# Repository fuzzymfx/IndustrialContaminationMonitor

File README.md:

Industrial pollutants are mainly discharged from various origins such as pulp and paper mills, chemical fertilizers, oil refineries, sugar factories, tanneries, textiles, steel, distilleries, fertilizers, pesticides, coal and mineral mining industries, drugs, glass, cement, petroleum, and engineering industries etc. 

Most of the industries dump via transporter to dumping places and thus there is no necessity for a check in the industry itself. The people staying nearby often utilize the same land and water for agricultural and daily purposes.  We believe that the industries should not take things lightly and especially for people staying nearby and the workers of the place a check should be there which when is necessary, warns the area of the contamination in soil and water. Industries have always had an intelligent solution about this. Dumping pipes always had a solvent which would dissolve the contamination if the level increases. This process is called neutralization But, this never gave the locals and the workers about information or statistical data about the amount of contamination currently present in the surroundings, instead all they get to know that the solvent is doing its job. We aim to target this problem by cost effective solutions.

We are trying to design a device which will measure the soil, water and air contamination in the area and warn the industries and local people when contamination limit exceeds. We are trying to make cost efficient product using IOT.
Budget:

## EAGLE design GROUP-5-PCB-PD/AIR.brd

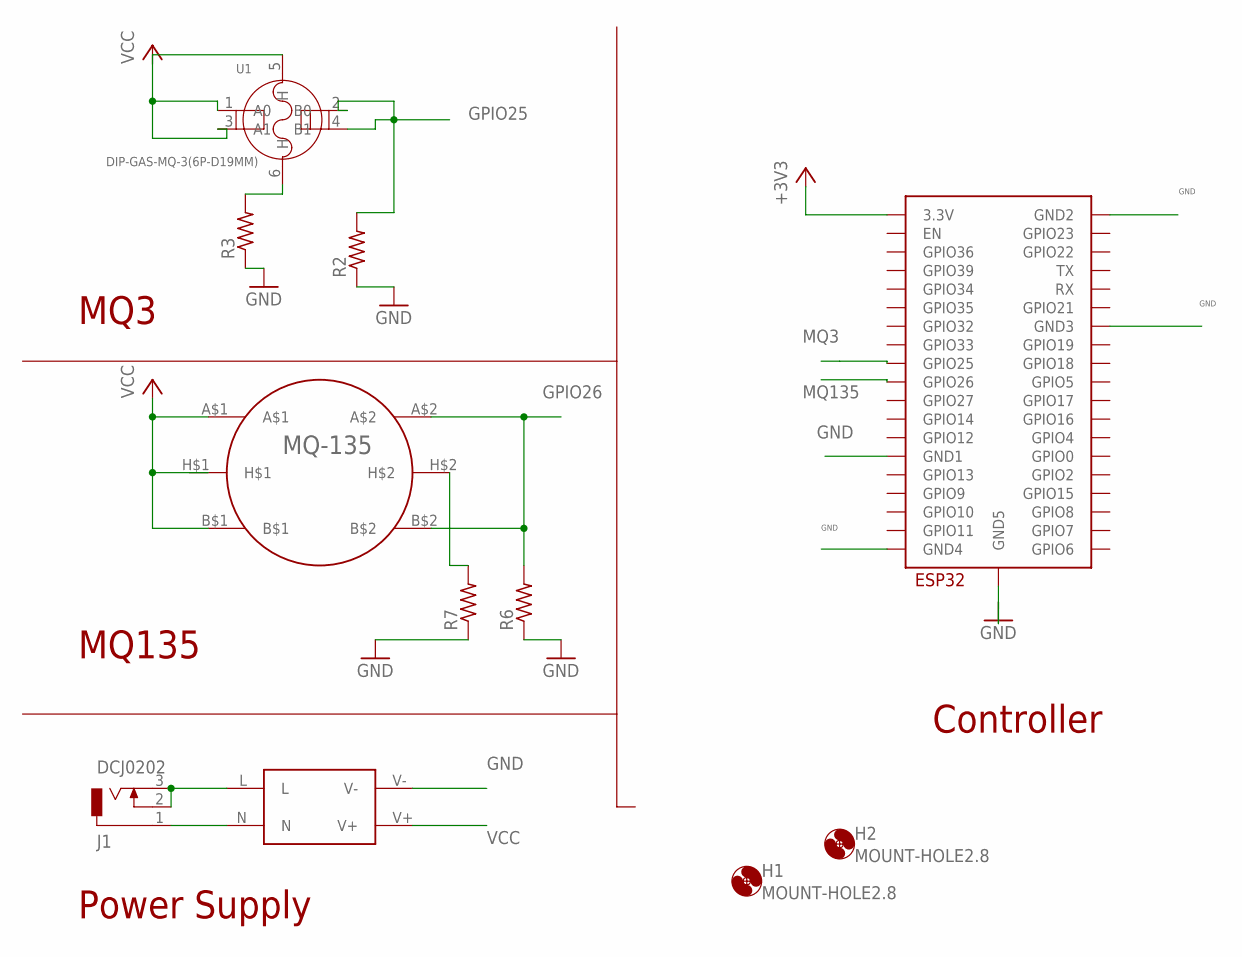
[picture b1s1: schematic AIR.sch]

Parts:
H1, H2: MOUNT-HOLE2.8; 2,8
J1: DCJ0202
R2, R3, R6, R7: R-US_0204/7; 0204/7
U1: DIP-GAS-MQ-3(6P-D19MM); SNR6-D19.0MM
U$1: ESP32-WROOM
U$2: HLK-PM01; HLK-PM01-PAK
U$3: MQ_135_A; MQ-135

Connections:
+3V3: U$1.3V3 (3.3V)
GND: R2.1, R3.1, R6.1, R7.1, U$1.GND1, U$1.GND2, U$1.GND3, U$1.GND4, U$1.GND5, U$2.V-
GPIO25: R2.2, U1.2 (B0), U1.4 (B1)
GPIO26: R6.2, U$3.A$2, U$3.B$2
MQ3: U$1.IO25 (GPIO25)
MQ135: U$1.IO26 (GPIO26)
unnamed: J1.2, J1.3, U$2.L
unnamed: R3.2, U1.6 (H)
unnamed: J1.1, U$2.N
unnamed: R7.2, U$3.H$2
VCC: U1.1 (A0), U1.3 (A1), U1.5 (H), U$2.V+, U$3.A$1, U$3.B$1, U$3.H$1

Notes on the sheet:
MQ3
MQ135
Power Supply
Controller

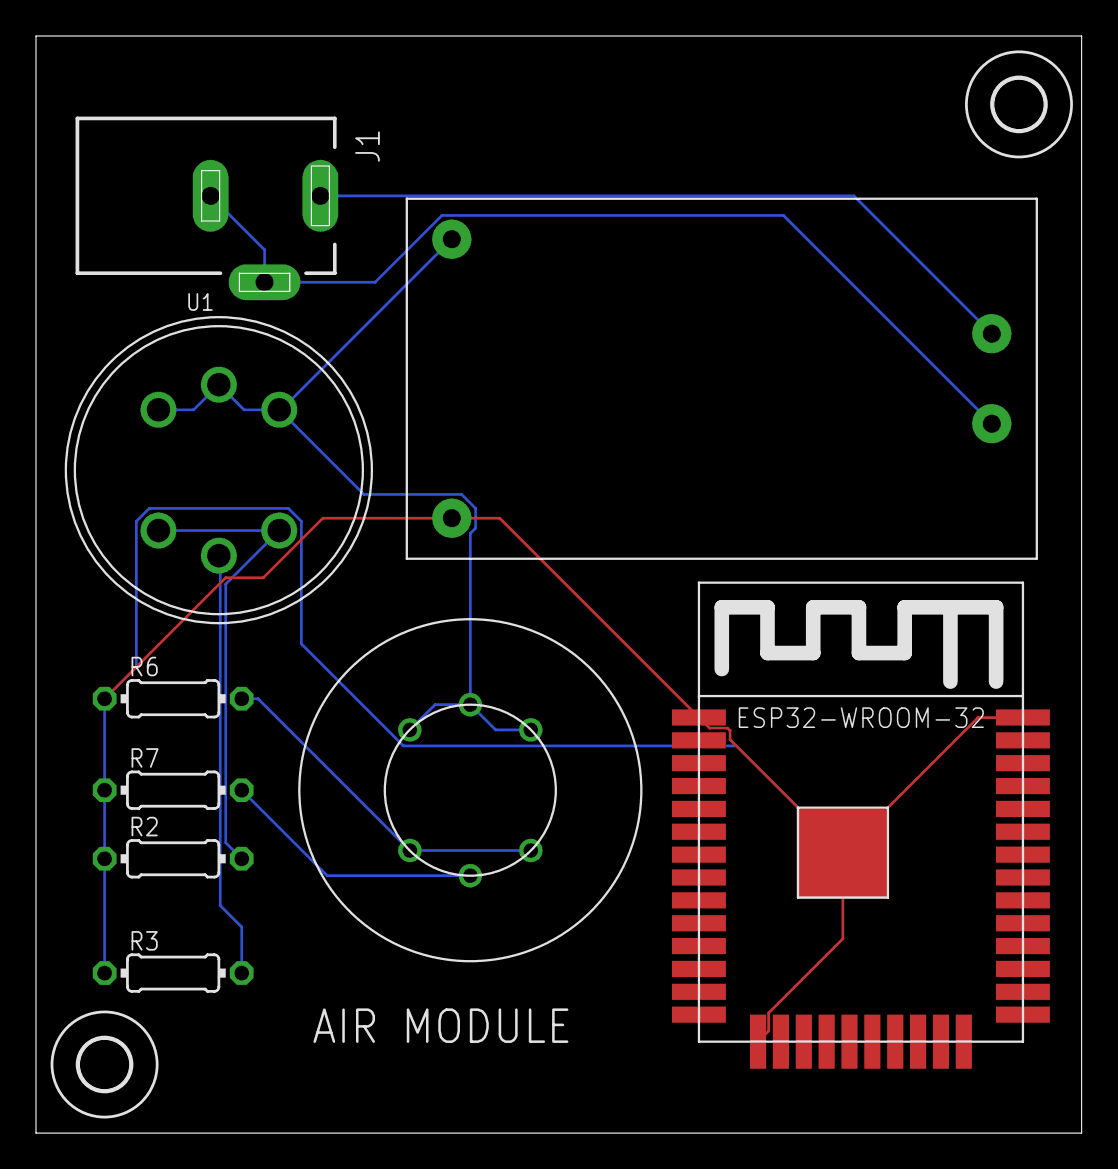
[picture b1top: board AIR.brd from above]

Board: 2 copper layers, 58.1 x 61.0 mm, 11 parts (0 on the bottom side), 8 nets.

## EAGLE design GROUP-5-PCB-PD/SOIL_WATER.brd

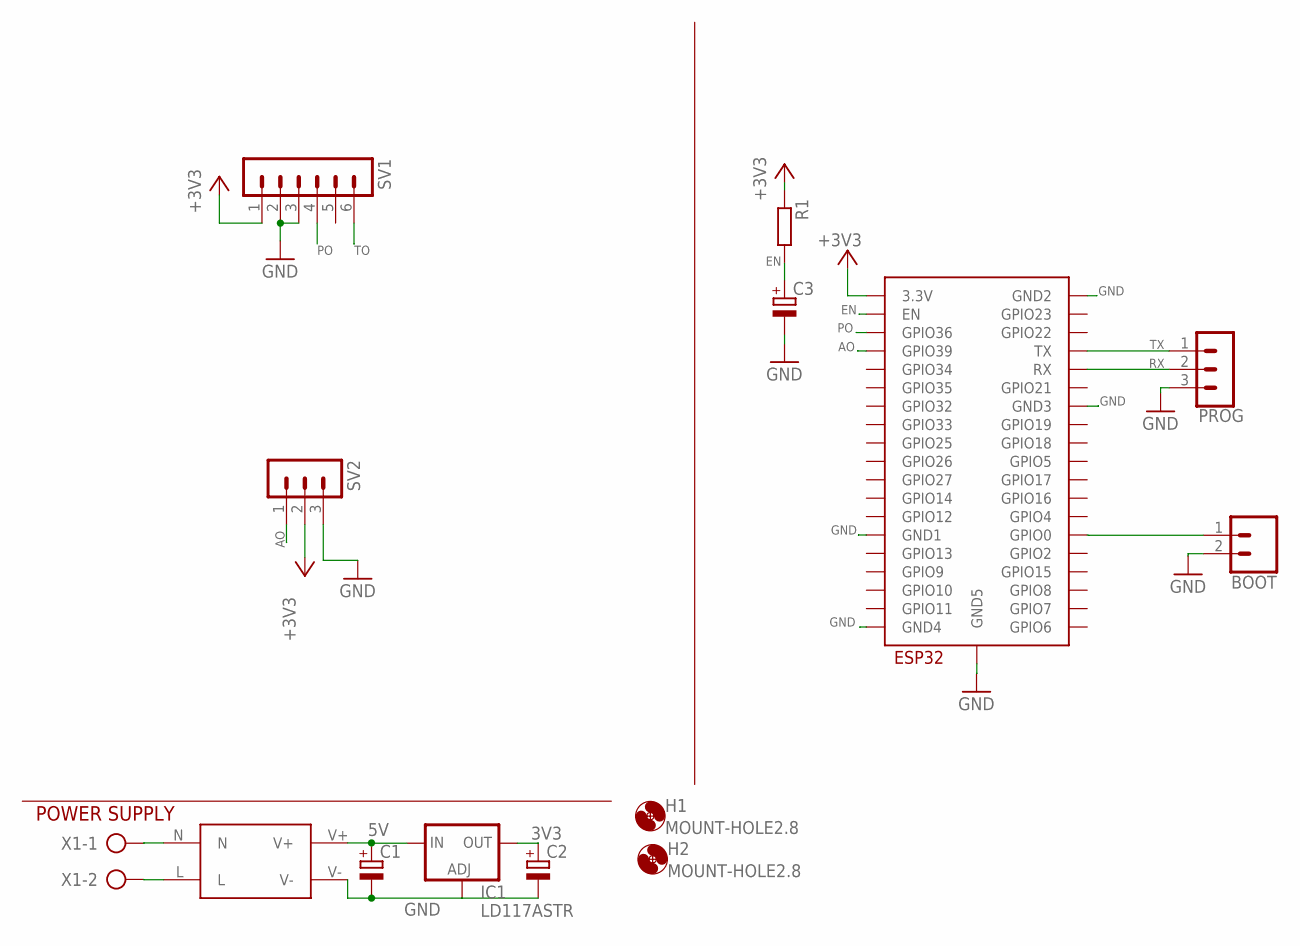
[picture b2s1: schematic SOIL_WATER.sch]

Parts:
BOOT: CONN_02; 1X02
C1, C2, C3: CPOL-EUE1.8-4; E1,8-4
H1, H2: MOUNT-HOLE2.8; 2,8
IC1: LD117ASTR; SOT223
PROG: MA03-1
R1: R-EU_0204/7; 0204/7
SV1: MA06-1
SV2: MA03-1
U$1: ESP32-WROOM
U$2: HLK-PM01; HLK-PM01-PAK
X1: AK500/2

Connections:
3V3: C2.+, IC1.4 (OUT)
5V: C1.+, IC1.3 (IN), U$2.V+
+3V3: R1.1, SV1.1, SV2.2, U$1.3V3 (3.3V)
AO: SV2.1, U$1.SENSOR_VN (GPIO39)
EN: C3.+, R1.2, U$1.EN
GND: BOOT.2, C1.-, C2.-, C3.-, IC1.1 (ADJ), PROG.3, SV1.2, SV1.3, SV2.3, U$1.GND1, U$1.GND2, U$1.GND3, U$1.GND4, U$1.GND5, U$2.V-
unnamed: U$2.N, X1.1
unnamed: U$2.L, X1.2
unnamed: BOOT.1, U$1.IO0 (GPIO0)
PO: SV1.4, U$1.SENSOR_VP (GPIO36)
RX: PROG.2, U$1.RX
TO: SV1.6
TX: PROG.1, U$1.TX

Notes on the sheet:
POWER SUPPLY

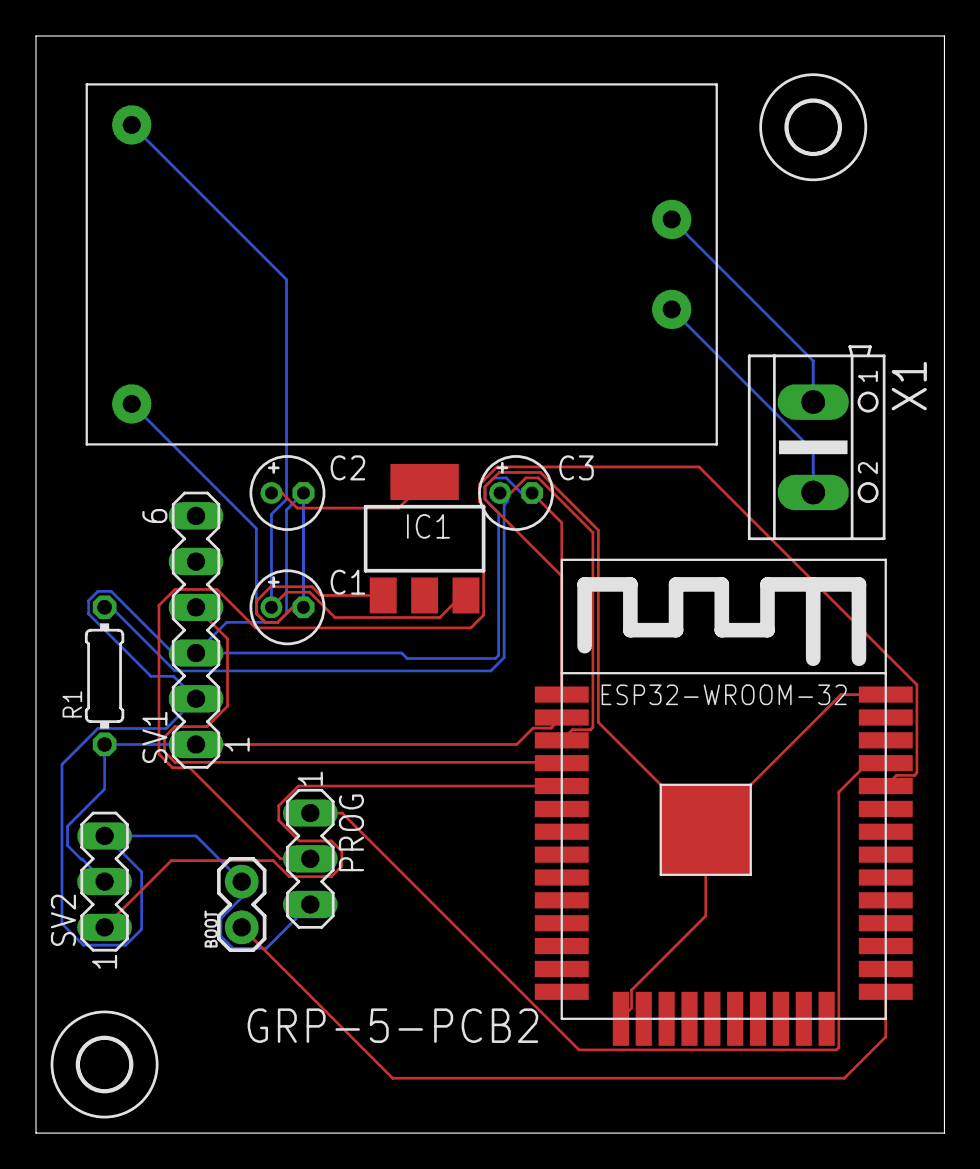
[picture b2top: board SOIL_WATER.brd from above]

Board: 2 copper layers, 50.5 x 61.0 mm, 14 parts (0 on the bottom side), 12 nets.

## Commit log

2021-06-11 Adding to github
2021-06-29 Final commit

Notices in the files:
parts and their libraries:
SparkFun-Connectors: Licensing: Creative Commons ShareAlike 4.0 International - https://creativecommons.org/licenses/by-sa/4.0
